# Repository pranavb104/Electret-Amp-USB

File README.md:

# Electret-Amp-USB
A simple transistor based amplifier for electret condenser type mics coupled with CM108b USB audio interface

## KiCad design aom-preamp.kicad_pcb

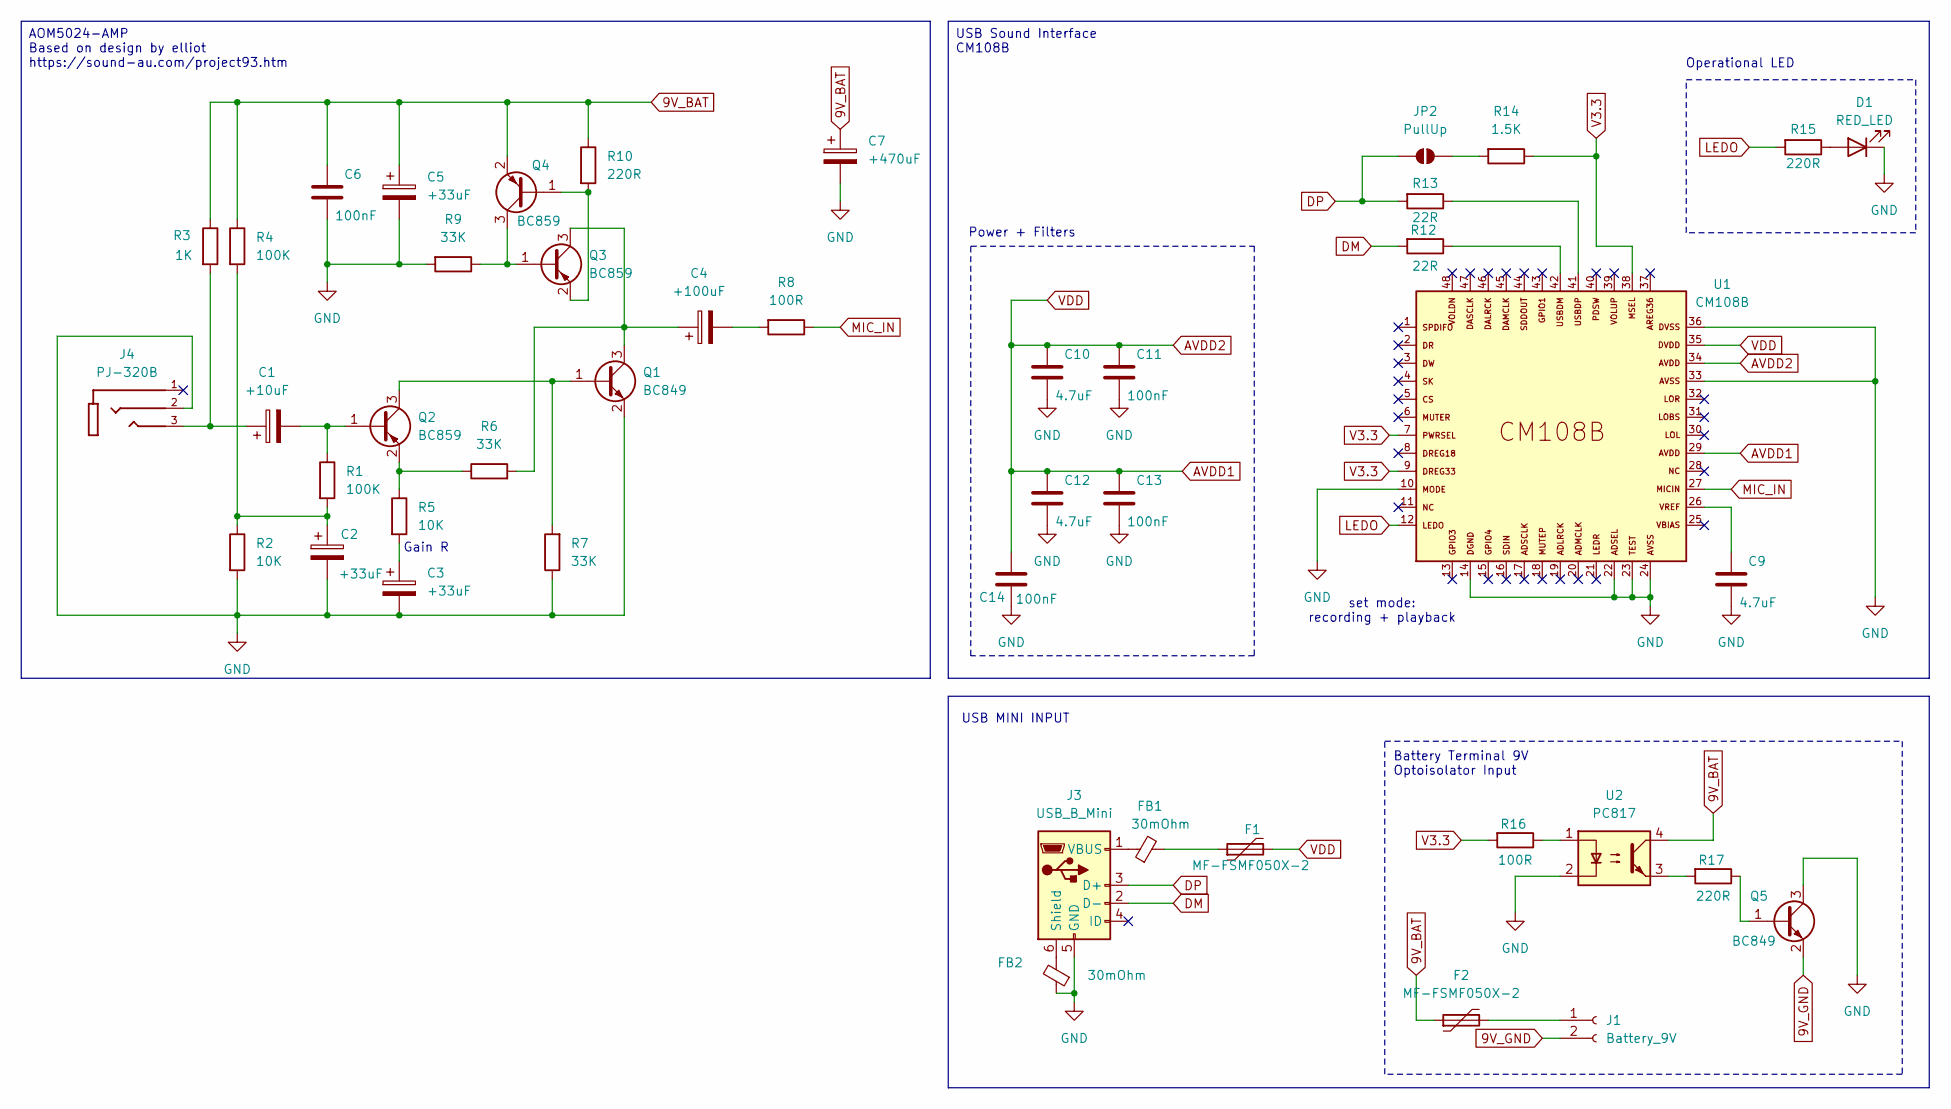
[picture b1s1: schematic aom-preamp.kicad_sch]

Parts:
C1: +10uF; CP_Elec_5x5.4
C2, C3, C5: +33uF; CP_Elec_5x5.4
C4: +100uF; CP_Elec_5x5.4
C6, C11, C13, C14: 100nF; C_0805_2012Metric
C7: +470uF; CP_Elec_6.3x7.7
C9, C10, C12: 4.7uF; C_0805_2012Metric
D1: RED_LED; LED_0603_1608Metric
F1, F2: MF-FSMF050X-2; Fuse_0603_1608Metric
FB1, FB2: 30mOhm; L_0603_1608Metric
J1: Battery_9V; JST_PH_B2B-PH-SM4-TB_1x02-1MP_P2.00mm_Vertical
J3: USB_B_Mini; USB_Mini-B_Wuerth_65100516121_Horizontal
J4: PJ-320B; BOOMELE_PJ-320B
JP2: PullUp; SolderJumper-2_P1.3mm_Open_RoundedPad1.0x1.5mm
Q1, Q5: BC849; SOT-23
Q2, Q3, Q4: BC859; SOT-23
R1, R4: 100K; R_0805_2012Metric
R2, R5: 10K; R_0805_2012Metric
R3: 1K; R_0805_2012Metric
R6, R7, R9: 33K; R_0805_2012Metric
R8, R16: 100R; R_0805_2012Metric
R10, R15, R17: 220R; R_0805_2012Metric
R12, R13: 22R; R_0805_2012Metric
R14: 1.5K; R_0805_2012Metric
U1: CM108B; TQFP48
U2: PC817; DIP-4_W7.62mm_SMDSocket_SmallPads

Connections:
9V_BAT: C5.1, C6.2, C7.1, F2.1, Q4.2 (E), R3.1, R4.1, R10.1, U2.4
9V_GND: J1.2, Q5.2 (E)
AVDD1: C10.2, C11.2, C12.2, C13.2, C14.1, F1.2, U1.29, U1.34, U1.35
DM: J3.2 (D-), R12.2
DP: J3.3 (D+), JP2.1 (A), R13.2
GND: C2.2, C3.2, C5.2, C6.1, C7.2, C9.1, C10.1, C11.1, C12.1, C13.1, C14.2, D1.1 (K), FB2.1, J3.5 (GND), J4.2, Q1.2 (E), Q5.3 (C), R2.2, R7.1, R9.2, U1.10, U1.14, U1.22, U1.23, U1.24, U1.33, U1.36, U2.2
LEDO: R15.2, U1.12
MIC_IN: R8.1, U1.27
unnamed: C1.1, J4.3, R3.2
unnamed: C2.1, R1.2, R2.1, R4.2
unnamed: C3.1, R5.2
unnamed: C4.2, R8.2
unnamed: C9.2, U1.26
unnamed: D1.2 (A), R15.1
unnamed: F1.1, FB1.2
unnamed: F2.2, J1.1
unnamed: FB2.2, J3.6 (Shield)
unnamed: FB1.1, J3.1 (VBUS)
unnamed: JP2.2 (B), R14.2
unnamed: Q1.1 (B), Q2.3 (C), R7.2
unnamed: C4.1, Q1.3 (C), Q3.3 (C), R6.2
unnamed: C1.2, Q2.1 (B), R1.1
unnamed: Q2.2 (E), R5.1, R6.1
unnamed: Q3.1 (B), Q4.3 (C), R9.1
unnamed: Q3.2 (E), Q4.1 (B), R10.2
unnamed: Q5.1 (B), R17.1
unnamed: R12.1, U1.42
unnamed: R13.1, U1.41
unnamed: R16.1, U2.1
unnamed: R17.2, U2.3
V3.3: R14.1, R16.2, U1.7, U1.9, U1.38

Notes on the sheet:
Operational LED
Battery Terminal 9V Optoisolator Input
set mode: recording + playback
USB MINI INPUT
Power + Filters
Gain R
USB Sound Interface CM108B
AOM5024-AMP Based on design by elliot https://sound-au.com/project93.htm

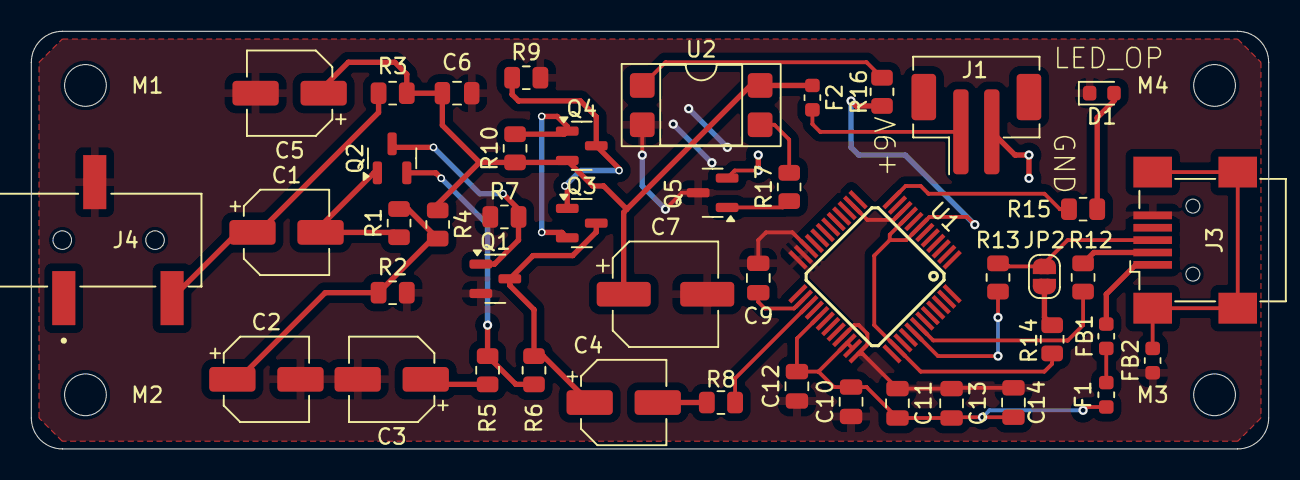
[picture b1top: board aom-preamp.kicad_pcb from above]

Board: 2 copper layers, 80.0 x 27.0 mm, 49 parts (0 on the bottom side), 31 nets.

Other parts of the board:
M1, M2, M3, M4: MountingHole_2.7mm_M2.5

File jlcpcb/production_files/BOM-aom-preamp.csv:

Comment,Designator,Footprint,LCSC,Quantity
100K,"R1,R4",R_0805_2012Metric,C149504,2
100R,"R16,R8",R_0805_2012Metric,C17408,2
10K,"R2,R5",R_0805_2012Metric,C17414,2
1K,R3,R_0805_2012Metric,C17513,1
220R,"R10,R15,R17",R_0805_2012Metric,C17557,3
22R,"R12,R13",R_0805_2012Metric,C17561,2
33K,"R6,R7,R9",R_0805_2012Metric,C17633,3
4.7uF,"C10,C12,C9",C_0805_2012Metric,C1779,3
Battery_9V,J1,JST_PH_B2B-PH-SM4-TB_1x02-1MP_P2.00mm_Vertical,C18077881,1
PJ-320B,J4,BOOMELE_PJ-320B,C18594,1
MF-FSMF050X-2,"F1,F2",Fuse_0603_1608Metric,C210357,2
RED_LED,D1,LED_0603_1608Metric,C2286,1
100nF,"C11,C13,C14,C6",C_0805_2012Metric,C28233,4
+10uF,C1,CP_Elec_5x5.4,C30110,1
BC849,"Q1,Q5",SOT-23,C334244,2
CM108B,U1,TQFP48,C371347,1
+100uF,C4,CP_Elec_5x5.4,C4054379,1
PC817,U2,DIP-4_W7.62mm_SMDSocket_SmallPads,C41807,1
1.5K,R14,R_0805_2012Metric,C4310,1
BC859,"Q2,Q3,Q4",SOT-23,C454952,3
+470uF,C7,CP_Elec_6.3x7.7,C5456765,1
USB_B_Mini,J3,USB_Mini-B_Wuerth_65100516121_Horizontal,C720611,1
30mOhm,"FB1,FB2",L_0603_1608Metric,C85831,2
+33uF,"C2,C3,C5",CP_Elec_5x5.4,C87866,3

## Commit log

2025-05-07 Update project files
2025-05-21 added 3D model
